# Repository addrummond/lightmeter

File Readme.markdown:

ARM gcc toolchain:

    https://launchpad.net/gcc-arm-embedded/+download

Programming known to work with OpenOCD 0.8.0.

See firmware/GDB_Readme.markdown.

Python 3 plus 'pypng' module required for build process.

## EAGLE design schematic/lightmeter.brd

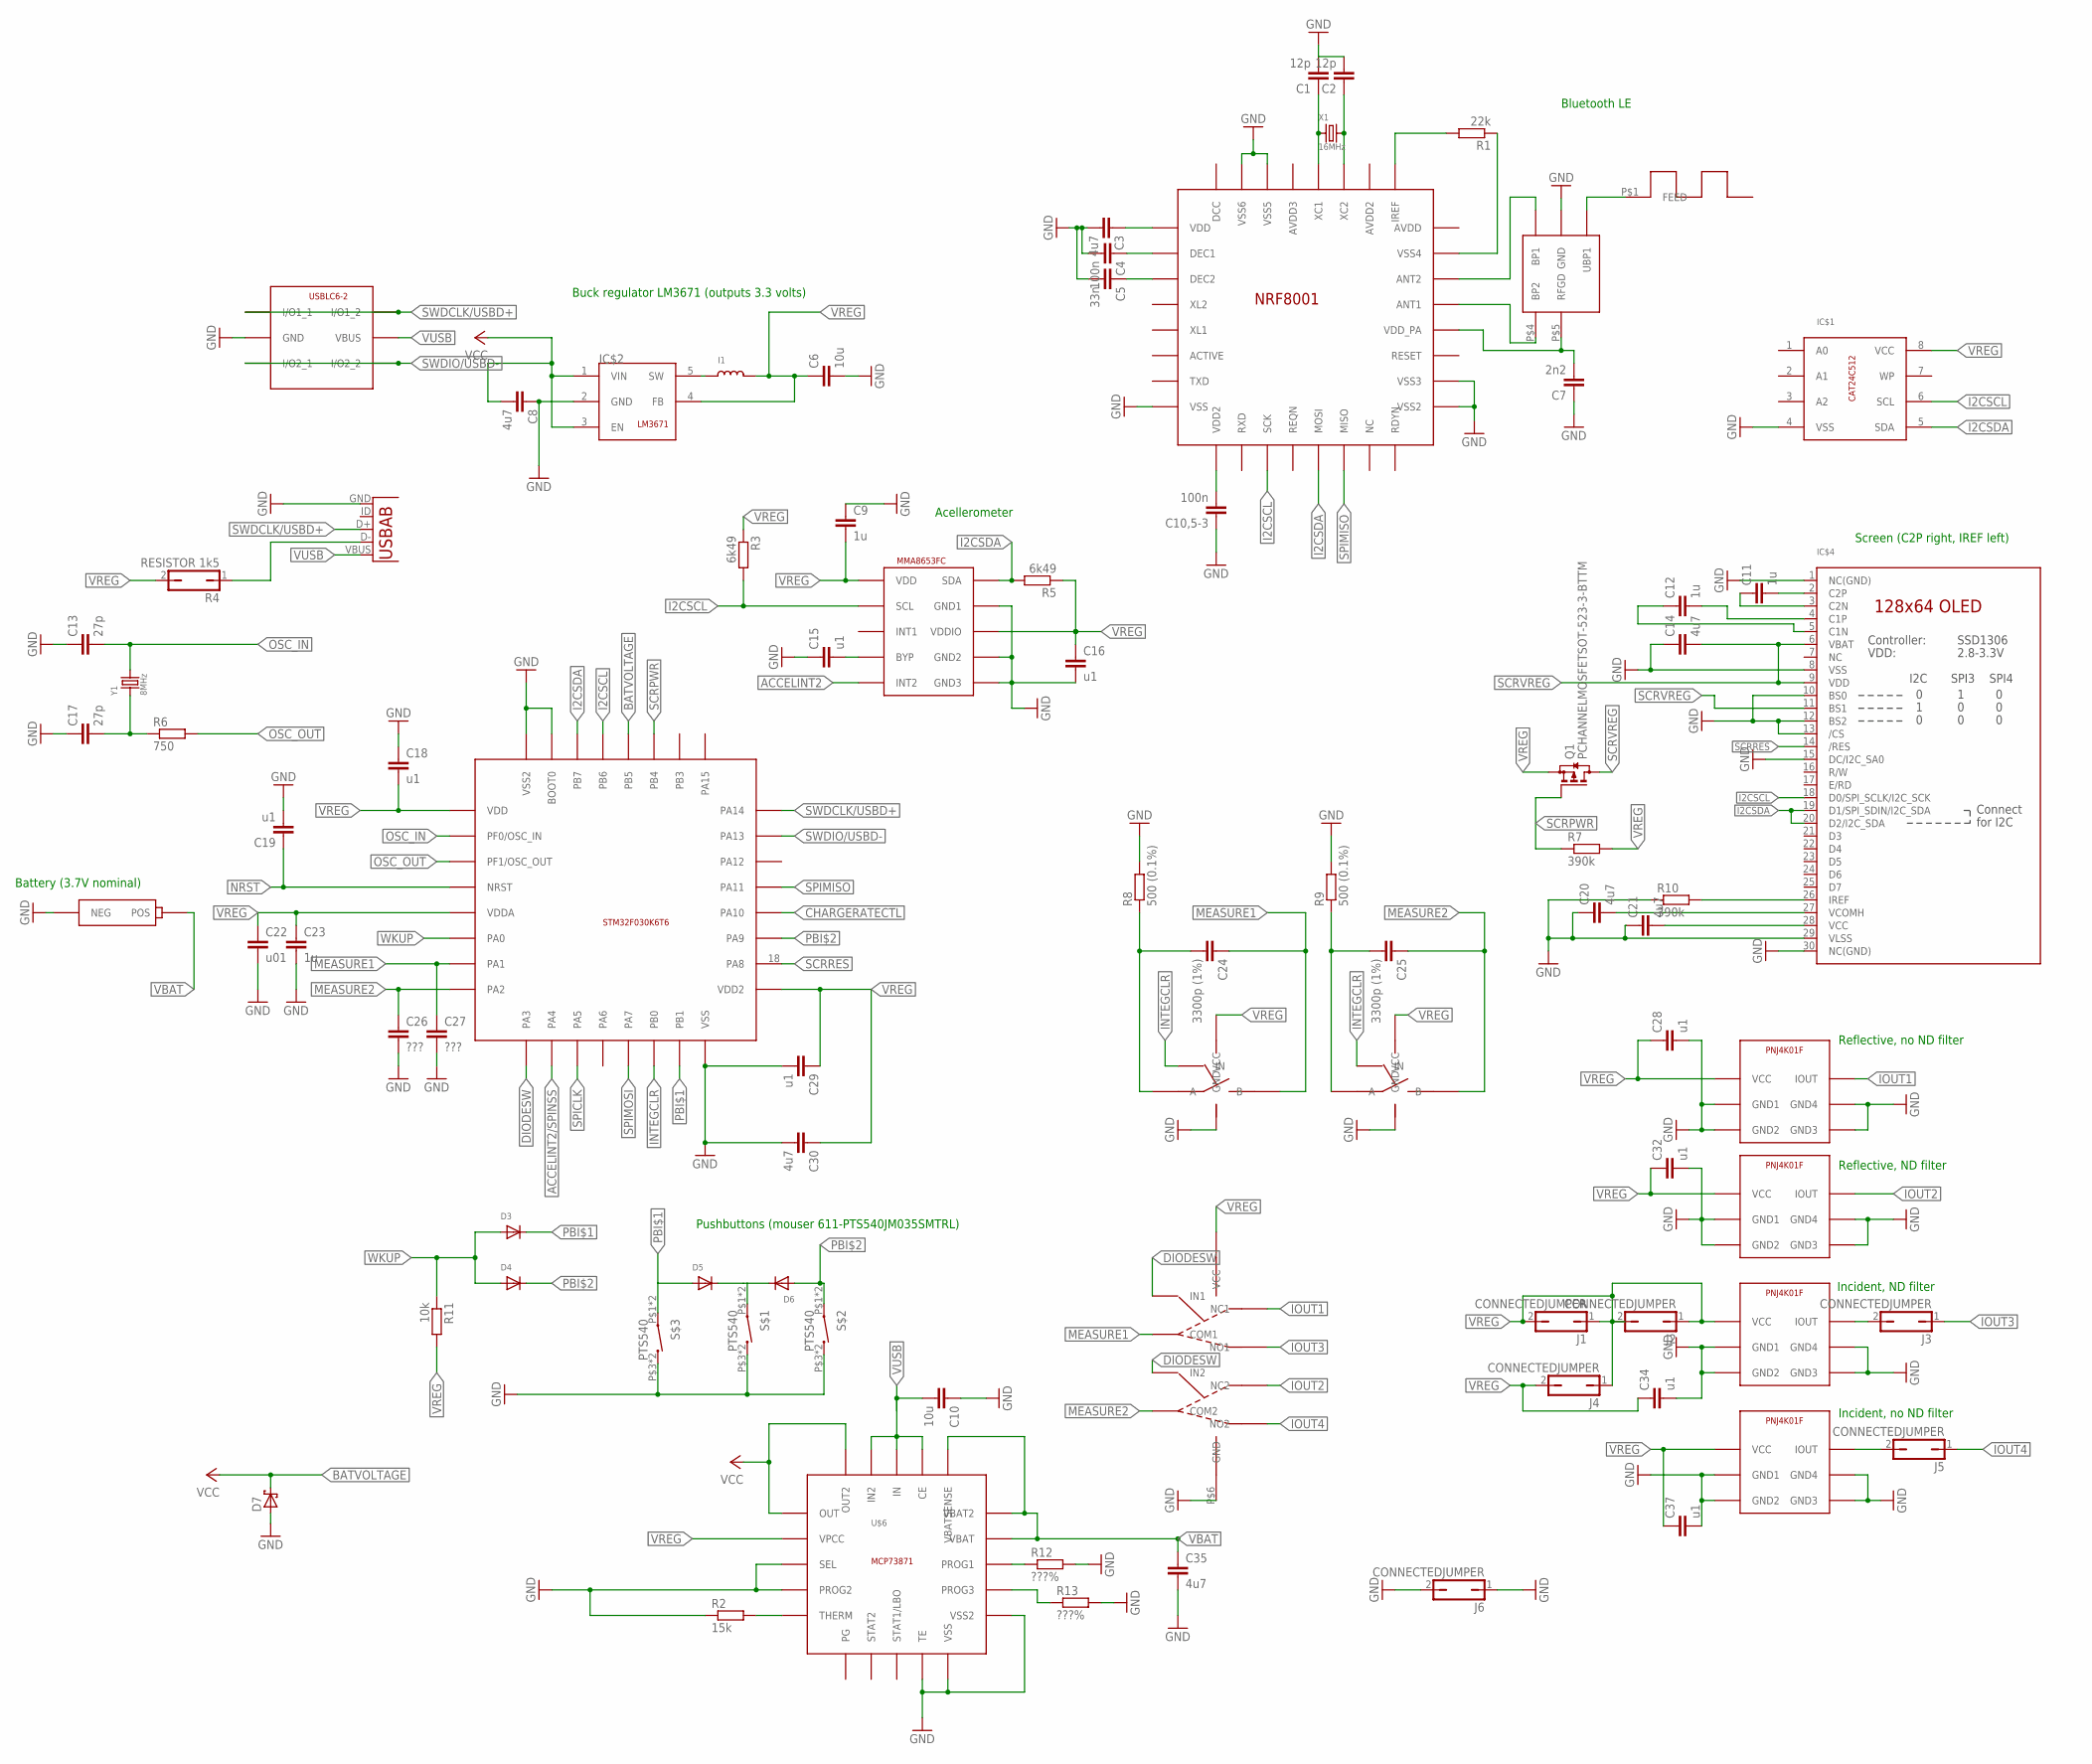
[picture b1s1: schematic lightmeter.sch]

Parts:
C1, C2: 12p; C0402
C3, C8, C14, C20, C21, C30, C35: 4u7; C0402
C4, C10,5-3: 100n; C0402
C5: 33n; C0402
C6: 10u; C0603
C7: 2n2; C0402
C9: 1u; C0603
C10: 10u; C0402
C11, C12: 1u; C0402
C13: 27p; GAP0402
C15, C16, C18, C19, C28, C29, C32, C34, C37: u1; C0402
C17: 27p; C0402
C22: u01; GAP0402
C23: 1u; GAP0603
C24, C25: 3300p (1%); C0603
C26, C27: ???; GAP0402
D3, D4, D5, D6: DIODESOD-323F; SOD-323F
D7: SCHOTTKY-DIODESOD-929; SOD-923
I1: CDRH2D14
IC$1: CAT24C512; TSSOP8
IC$2: LM3671; SOT23-5
IC$3: MMA8653; DFN-10
IC$4: DISP_OLED_UG-2864HSWEG010.96"; UG-2864HSWEG01_0.96IN_WRAPAROUND
IC$5: STM32F030K6T6; QFP-32
IC$6, IC$7: SN74LVC1G66; SOT-553-5
IC$8, IC$9, IC$11, IC$13: PNJ4K01F
IC$12: NLAS5223B; WQFN10
J1, J2, J3, J4, J5, J6: CONNECTEDJUMPER; JUMPER_R0402
Q1: PCHANNELMOSFETSOT-523-3-BTTM; SOT-523-3-BTTM
R1: 22k; R0402
R2: 15k; R0402
R3, R5: 6k49; R0402
R4: RESISTOR 1k5; JUMPER_R0402
R6: 750; R0402
R7, R10: 390k; R0402
R8, R9: 500 (0.1%); R0402
R11: 10k; R0402
R12, R13: ???%; R0402
S$1, S$2, S$3: PTS540; PTS540BTM
U1: USB-ABUSB-AB-MICRO-MIDMOUNT; USB-AB-MICRO-MIDMOUNT
U$1: 2450AT18A100
U$2: 2450BM14A00022450BM14A0002; 2450BM14A0002
U$3: NRF8001
U$4: USBLC6-2; SOT666
U$5: LIBAT; 78171-0002
U$6: MCP73871; QFN20
X1: 16MHz; CRYSTAL-2X1.6
Y1: 8MHz; CRYSTAL3.2X5MM

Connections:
ACCELINT2: IC$3.P$5 (INT2)
ACCELINT2/SPINSS: IC$5.10 (PA4)
ANT1CON: U$2.P$4 (BP2), U$3.P$21 (ANT1)
ANT2CON: U$2.P$3 (BP1), U$3.P$22 (ANT2)
ANTTRACE: U$1.P$1, U$2.P$1 (UBP1)
BATVOLTAGE: D7.P$2 (C), IC$5.28 (PB5)
CHARGERATECTL: IC$5.20 (PA10)
DIODESW: IC$5.9 (PA3), IC$12.P$4 (IN1), IC$12.P$8 (IN2)
GND: C1.2, C2.2, C3.2, C4.2, C5.2, C6.2, C7.1, C8.1, C9.1, C10.1, C10,5-3.1, C13.1, C14.1, C15.1, C16.2, C17.1, C18.1, C19.2, C20.1, C21.1, C22.2, C23.2, C26.2, C27.2, C28.2, C29.2, C30.2, C32.2, C34.2, C35.2, C37.2, D7.P$1 (A), IC$1.4 (VSS), IC$2.2 (GND), IC$3.P$6 (GND3), IC$3.P$7 (GND2), IC$3.P$9 (GND1), IC$4.1 (NC(GND)), IC$4.8 (VSS), IC$4.10 (BS0), IC$4.12 (BS2), IC$4.13 (/CS), IC$4.15 (DC/I2C_SA0), IC$4.29 (VLSS), IC$4.30 (NC(GND)), IC$5.16 (VSS), IC$5.31 (BOOT0), IC$5.32 (VSS2), IC$6.P$3 (GND), IC$7.P$3 (GND), IC$8.P$2 (GND1), IC$8.P$3 (GND2), IC$8.P$4 (GND3), IC$8.P$5 (GND4), IC$9.P$2 (GND1), IC$9.P$3 (GND2), IC$9.P$4 (GND3), IC$9.P$5 (GND4), IC$11.P$2 (GND1), IC$11.P$3 (GND2), IC$11.P$4 (GND3), IC$11.P$5 (GND4), IC$12.P$6 (GND), IC$13.P$2 (GND1), IC$13.P$3 (GND2), IC$13.P$4 (GND3), IC$13.P$5 (GND4), J6.1, J6.2, R2.1, R8.2, R9.2, R10.1, R12.2, R13.2, S$1.P$3 (2), S$1.P$4 (2), S$2.P$3 (2), S$2.P$4 (2), S$3.P$3 (2), S$3.P$4 (2), U1.GND, U$2.P$2 (GND), U$3.P$8 (VSS), U$3.P$17 (VSS2), U$3.P$18 (VSS3), U$3.P$30 (VSS5), U$3.P$31 (VSS6), U$3.P$33 (VSS), U$4.P$2 (GND), U$5.P$1 (NEG), U$6.P$3 (SEL), U$6.P$4 (PROG2), U$6.P$9 (TE), U$6.P$10 (VSS), U$6.P$11 (VSS2), U$6.P$21 (VSS2)
I2CSCL: IC$1.6 (SCL), IC$3.P$2 (SCL), IC$4.18 (D0/SPI_SCLK/I2C_SCK), IC$5.29 (PB6), R3.2, U$3.P$11 (SCK)
I2CSDA: IC$1.5 (SDA), IC$3.P$10 (SDA), IC$4.19 (D1/SPI_SDIN/I2C_SDA), IC$4.20 (D2/I2C_SDA), IC$5.30 (PB7), R5.2, U$3.P$13 (MOSI)
INTEGCLR: IC$5.14 (PB0), IC$6.P$4 (IN), IC$7.P$4 (IN)
IOUT1: IC$8.P$6 (IOUT), IC$12.P$5 (NC1)
IOUT2: IC$9.P$6 (IOUT), IC$12.P$7 (NC2)
IOUT3: IC$12.P$2 (NO1), J3.1
IOUT4: IC$12.P$10 (NO2), J5.1
MEASURE1: C24.1, C27.1, IC$5.7 (PA1), IC$6.P$2 (B), IC$12.P$3 (COM1)
MEASURE2: C25.1, C26.1, IC$5.8 (PA2), IC$7.P$2 (B), IC$12.P$9 (COM2)
unnamed: IC$11.P$6 (IOUT), J3.2
unnamed: IC$13.P$6 (IOUT), J5.2
unnamed: C24.2, IC$6.P$1 (A), R8.1
unnamed: R2.2, U$6.P$5 (THERM)
unnamed: C25.2, IC$7.P$1 (A), R9.1
unnamed: C15.2, IC$3.P$4 (BYP)
unnamed: C17.2, R6.1, Y1.P$1 (1)
unnamed: I1.P$1 (1), IC$2.5 (SW)
unnamed: C20.2, IC$4.27 (VCOMH)
unnamed: D5.C, D6.C, S$1.P$1 (1), S$1.P$2 (1)
unnamed: C11.2, IC$4.2 (C2P)
unnamed: C11.1, IC$4.3 (C2N)
unnamed: C7.2, U$2.P$5 (RFGD), U$3.P$20 (VDD_PA)
unnamed: R1.2, U$3.P$25 (IREF)
unnamed: IC$4.26 (IREF), R10.2
unnamed: R1.1, U$3.P$23 (VSS4)
unnamed: C5.1, U$3.P$3 (DEC2)
unnamed: C3.1, U$3.P$1 (VDD)
unnamed: C10,5-3.2, U$3.P$9 (VDD2)
unnamed: C12.1, IC$4.5 (C1N)
unnamed: C4.1, U$3.P$2 (DEC1)
unnamed: C1.1, U$3.P$28 (XC1), X1.P$1 (1)
unnamed: C12.2, IC$4.4 (C1P)
unnamed: C2.1, U$3.P$27 (XC2), X1.P$3 (2)
unnamed: C21.2, IC$4.28 (VCC)
unnamed: R12.1, U$6.P$13 (PROG1)
unnamed: R13.1, U$6.P$12 (PROG3)
NRST: C19.1, IC$5.4 (NRST)
OSC_IN: C13.2, IC$5.2 (PF0/OSC_IN), Y1.P$2 (2)
OSC_OUT: IC$5.3 (PF1/OSC_OUT), R6.2
PBI$1: D3.C, D5.A, IC$5.15 (PB1), S$3.P$1 (1), S$3.P$2 (1)
PBI$2: D4.C, D6.A, IC$5.19 (PA9), S$2.P$1 (1), S$2.P$2 (1)
SCRPWR: IC$5.27 (PB4), Q1.P$3 (G), R7.1
SCRRES: IC$4.14 (/RES), IC$5.18 (PA8)
SCRVREG: C14.2, IC$4.6 (VBAT), IC$4.9 (VDD), IC$4.11 (BS1), Q1.P$1 (D)
SPICLK: IC$5.11 (PA5)
SPIMISO: IC$5.21 (PA11), U$3.P$14 (MISO)
SPIMOSI: IC$5.13 (PA7)
SWDCLK/USBD+: IC$5.24 (PA14), U1.D+, U$4.P$1 (I/O1_1), U$4.P$6 (I/O1_2)
SWDIO/USBD-: IC$5.23 (PA13), U$4.P$3 (I/O2_1), U$4.P$4 (I/O2_2)
USBD-: R4.1, U1.D-
VBAT: C35.1, U$5.P$2 (POS), U$6.P$14 (VBAT), U$6.P$15 (VBAT2), U$6.P$16 (VBATSENSE)
VCC: C8.2, IC$2.1 (VIN), IC$2.3 (EN), U$6.P$1 (OUT), U$6.P$20 (OUT2)
VREG: C6.1, C9.2, C16.1, C18.2, C22.1, C23.1, C28.1, C29.1, C30.1, C32.1, C34.1, C37.1, I1.P$2 (2), IC$1.8 (VCC), IC$2.4 (FB), IC$3.P$1 (VDD), IC$3.P$8 (VDDIO), IC$5.1 (VDD), IC$5.5 (VDDA), IC$5.17 (VDD2), IC$6.P$5 (VCC), IC$7.P$5 (VCC), IC$8.P$1 (VCC), IC$9.P$1 (VCC), IC$11.P$1 (VCC), IC$12.P$1 (VCC), IC$13.P$1 (VCC), J1.1, J1.2, J2.1, J2.2, J4.1, J4.2, Q1.P$2 (S), R3.1, R4.2, R5.1, R7.2, R11.2, U$6.P$2 (VPCC)
VUSB: C10.2, U1.VBUS, U$4.P$5 (VBUS), U$6.P$17 (CE), U$6.P$18 (IN), U$6.P$19 (IN2)
WKUP: D3.A, D4.A, IC$5.6 (PA0), R11.1

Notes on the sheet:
Battery (3.7V nominal)
Buck regulator LM3671 (outputs 3.3 volts)
Pushbuttons (mouser 611-PTS540JM035SMTRL)
Screen (C2P right, IREF left)
Acellerometer
Reflective, no ND filter
Reflective, ND filter
Incident, ND filter
Incident, no ND filter
Bluetooth LE

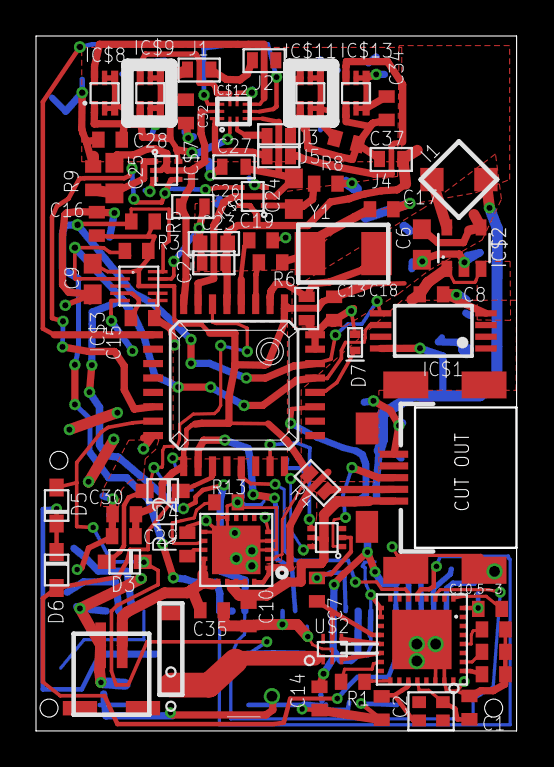
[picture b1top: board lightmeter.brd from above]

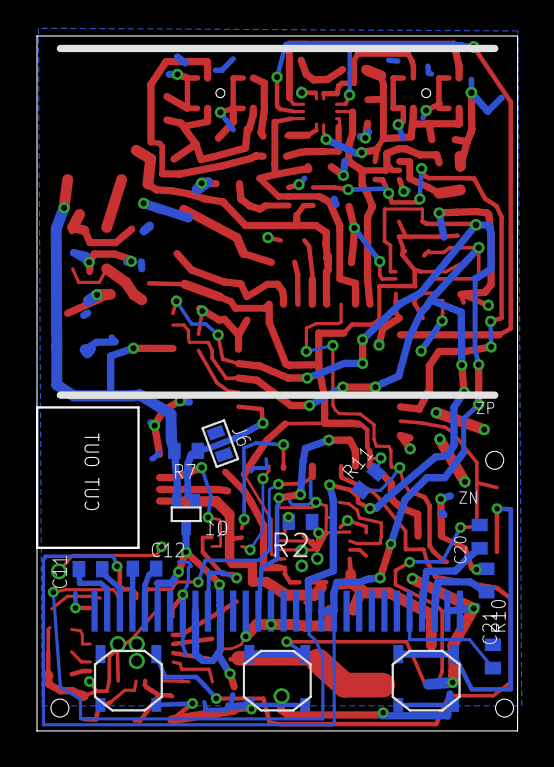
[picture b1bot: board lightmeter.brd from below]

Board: 2 copper layers, 26.7 x 38.6 mm, 85 parts (9 on the bottom side), 59 nets.

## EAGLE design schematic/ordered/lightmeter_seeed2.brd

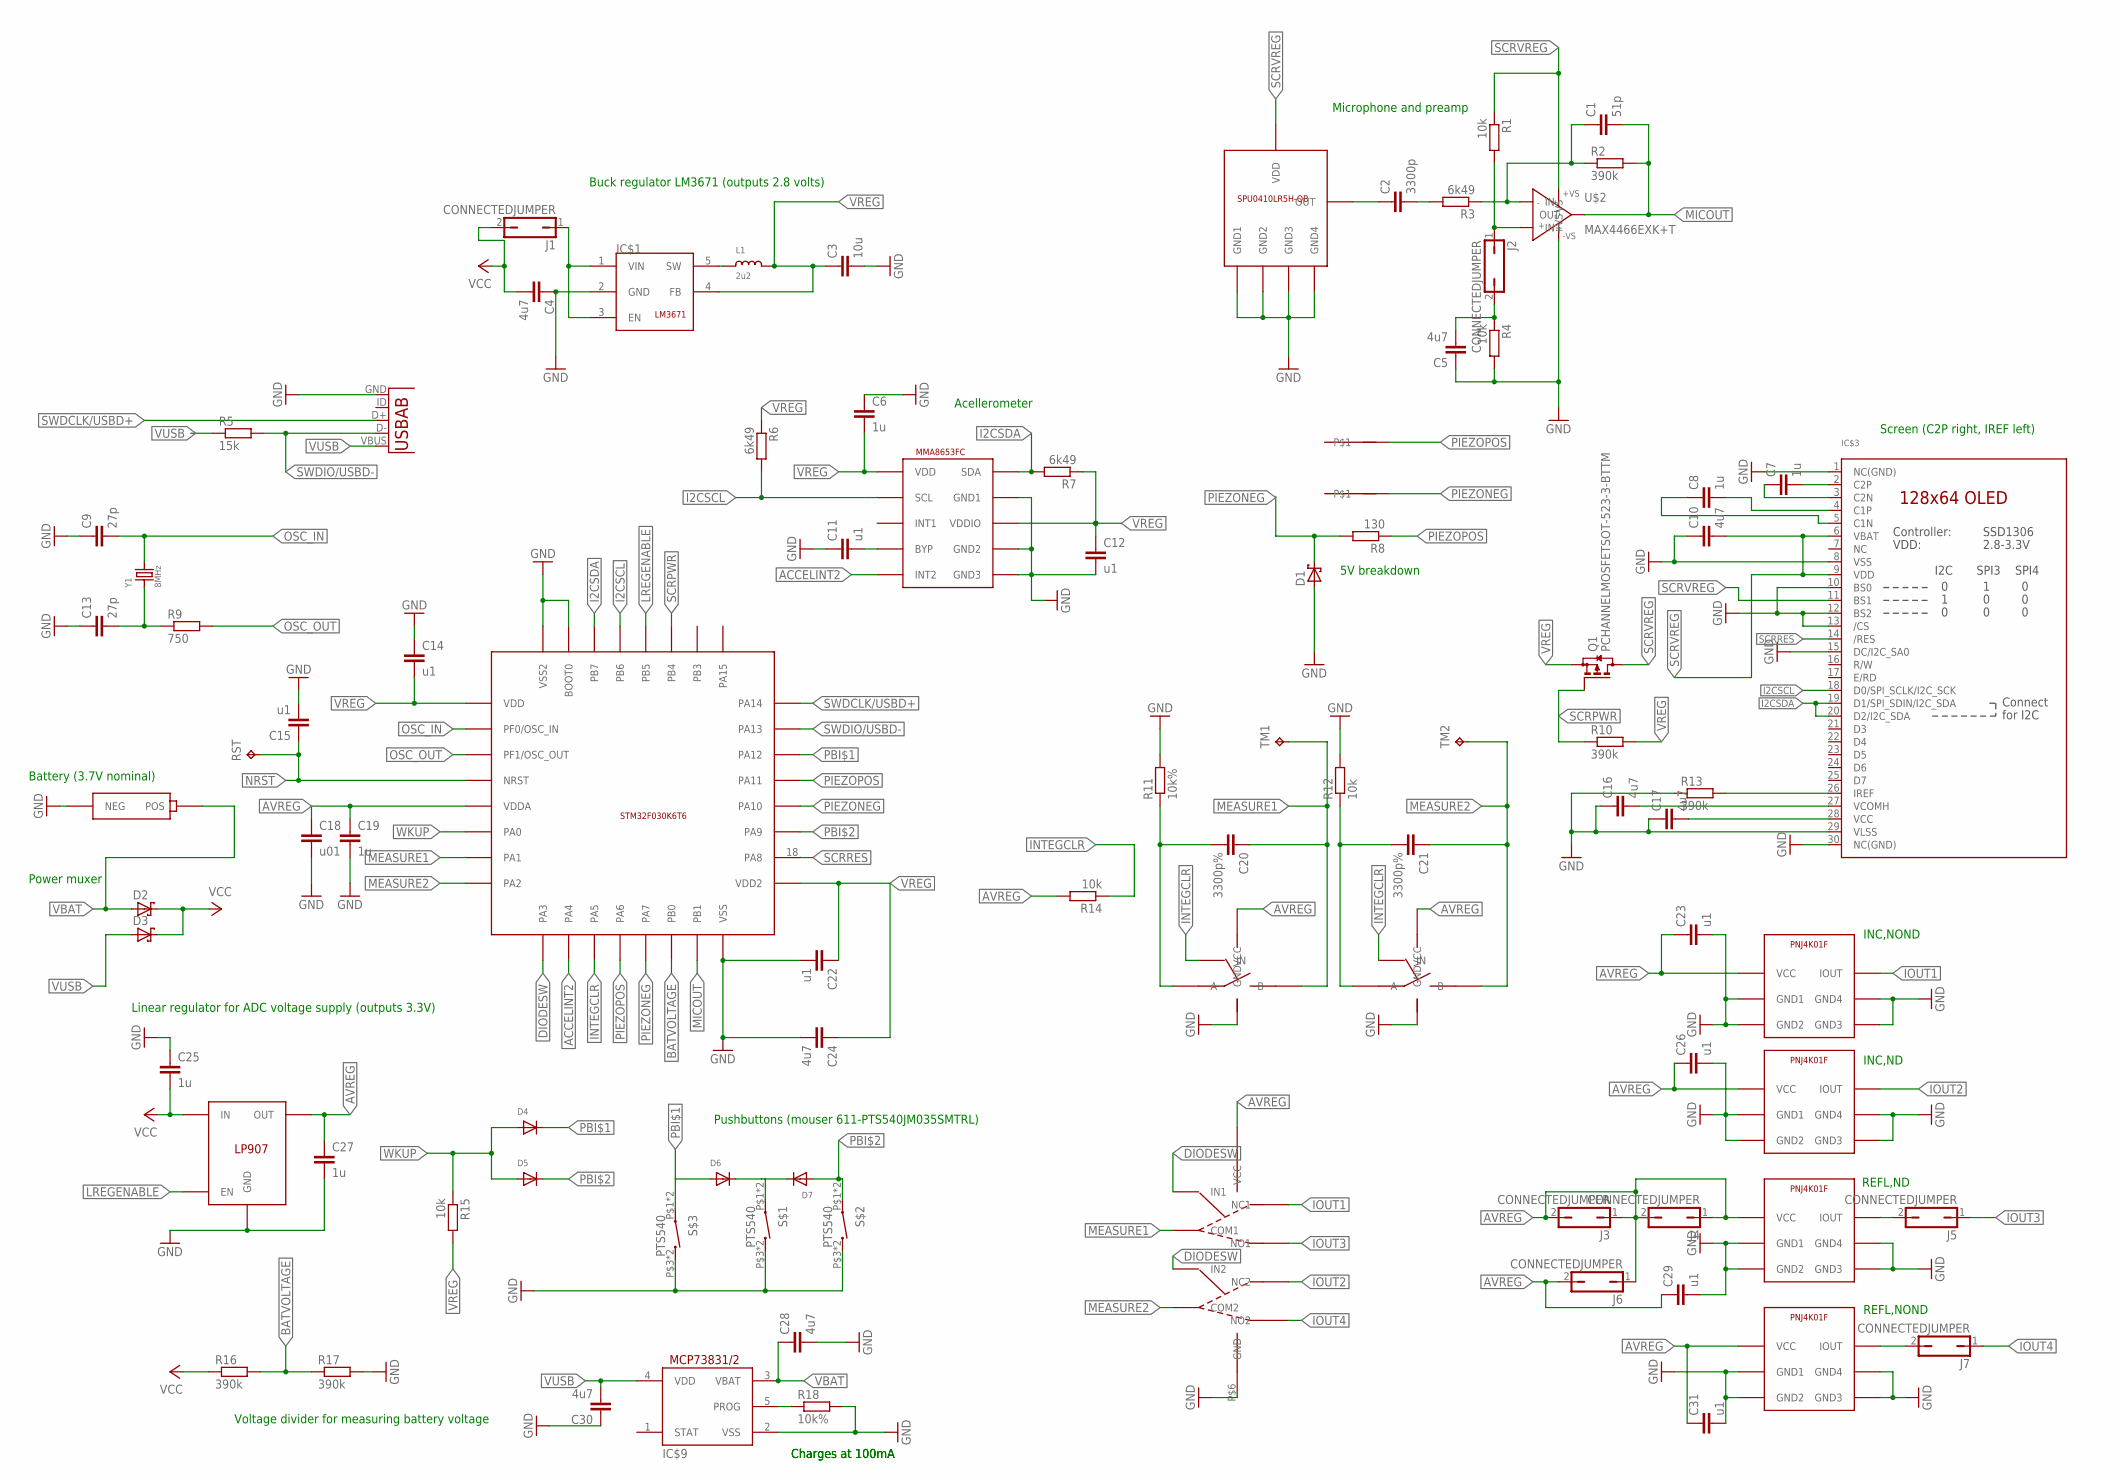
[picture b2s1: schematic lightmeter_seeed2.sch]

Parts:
C1: 51p; C0402
C2: 3300p; C0603
C3: 10u; C0402
C4, C5, C10, C16, C17, C24, C28, C30: 4u7; C0402
C6, C7, C8, C25, C27: 1u; C0603
C9: 27p; GAP0402
C11, C12, C14, C15, C22, C23, C26, C29, C31: u1; C0402
C13: 27p; C0402
C18: u01; GAP0402
C19: 1u; GAP0603
C20, C21: 3300p%; C0603
D1: SCHOTTKY-DIODESOD-923-BTTM; SOD-923-BTTM
D2, D3: SCHOTTKY-DIODESC-79; SC-79
D4, D5, D6, D7: DIODESOD-323F; SOD-323F
IC$1: LM3671; SOT23-5
IC$2: MMA8653; DFN-10
IC$3: DISP_OLED_UG-2864HSWEG010.96"; UG-2864HSWEG01_0.96IN_WRAPAROUND
IC$4: STM32F030K6T6; QFP-32
IC$5, IC$7, IC$8, IC$10: PNJ4K01F
IC$6: LP5907; SOT23-5L
IC$9: MCP73831/OT; SOT23-5L
J1, J2, J3, J4, J5, J6, J7: CONNECTEDJUMPER; JUMPER_R0402
L1: 2u2; _0603
Q1: PCHANNELMOSFETSOT-523-3-BTTM; SOT-523-3-BTTM
R1, R4, R12, R14, R15: 10k; R0402
R2, R10, R13, R17: 390k; R0402
R3, R6, R7: 6k49; R0402
R5: 15k; R0402
R8: 130; R0402
R9: 750; R0402
R11, R18: 10k%; R0402
R16: 390k; JUMPER_R0402
RST: TPB1,27; B1,27
S$1, S$2, S$3: PTS540; PTS540BTM
TM1, TM2: TPB1,27; B1,27
U1: USB-ABUSB-AB-MICRO-MIDMOUNT; USB-AB-MICRO-MIDMOUNT
U$1: SPU0410LR5H-QBSPU0410LRSH-QB; SPU0410LR5H-QB
U$2: MAX4466EXK+T; SC-70-5
U$3: LIBAT; 78171-0002
U$4, U$5: SN74LVC1G66; SOT-553-5
U$6: NLAS5223B; WQFN10
Y1: 8MHz; CRYSTAL3.2X5MM
ZN: WIREATTACHMENT; SMALLSQUAREWIREHOLE
ZP: WIREATTACHMENT; SMALLSQUAREWIREHOLE

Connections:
ACCELINT2: IC$2.P$5 (INT2), IC$4.10 (PA4)
AVREG: C18.1, C19.1, C23.1, C26.1, C27.1, C29.1, C31.1, IC$4.5 (VDDA), IC$5.P$1 (VCC), IC$6.5 (OUT), IC$7.P$1 (VCC), IC$8.P$1 (VCC), IC$10.P$1 (VCC), J3.1, J3.2, J4.1, J4.2, J6.1, J6.2, R14.2, U$4.P$5 (VCC), U$5.P$5 (VCC), U$6.P$1 (VCC)
BATVOLTAGE: IC$4.14 (PB0), R16.2, R17.1
DIODESW: IC$4.9 (PA3), U$6.P$4 (IN1), U$6.P$8 (IN2)
GND: C3.2, C4.1, C5.1, C6.1, C9.1, C10.1, C11.1, C12.2, C13.1, C14.1, C15.2, C16.1, C17.1, C18.2, C19.2, C22.2, C23.2, C24.2, C25.1, C26.2, C27.2, C28.2, C29.2, C30.1, C31.2, D1.P$1 (A), IC$1.2 (GND), IC$2.P$6 (GND3), IC$2.P$7 (GND2), IC$2.P$9 (GND1), IC$3.1 (NC(GND)), IC$3.8 (VSS), IC$3.10 (BS0), IC$3.12 (BS2), IC$3.13 (/CS), IC$3.15 (DC/I2C_SA0), IC$3.29 (VLSS), IC$3.30 (NC(GND)), IC$4.16 (VSS), IC$4.31 (BOOT0), IC$4.32 (VSS2), IC$5.P$2 (GND1), IC$5.P$3 (GND2), IC$5.P$4 (GND3), IC$5.P$5 (GND4), IC$6.2 (GND), IC$7.P$2 (GND1), IC$7.P$3 (GND2), IC$7.P$4 (GND3), IC$7.P$5 (GND4), IC$8.P$2 (GND1), IC$8.P$3 (GND2), IC$8.P$4 (GND3), IC$8.P$5 (GND4), IC$9.2 (VSS), IC$10.P$2 (GND1), IC$10.P$3 (GND2), IC$10.P$4 (GND3), IC$10.P$5 (GND4), R4.2, R11.2, R12.2, R13.1, R17.2, R18.2, S$1.P$3 (2), S$1.P$4 (2), S$2.P$3 (2), S$2.P$4 (2), S$3.P$3 (2), S$3.P$4 (2), U1.GND, U$1.P$2 (GND1), U$1.P$3 (GND2), U$1.P$5 (GND3), U$1.P$6 (GND4), U$2.P$2 (-VS), U$3.P$1 (NEG), U$4.P$3 (GND), U$5.P$3 (GND), U$6.P$6 (GND)
I2CSCL: IC$2.P$2 (SCL), IC$3.18 (D0/SPI_SCLK/I2C_SCK), IC$4.29 (PB6), R6.2
I2CSDA: IC$2.P$10 (SDA), IC$3.19 (D1/SPI_SDIN/I2C_SDA), IC$3.20 (D2/I2C_SDA), IC$4.30 (PB7), R7.2
INTEGCLR: IC$4.11 (PA5), R14.1, U$4.P$4 (IN), U$5.P$4 (IN)
IOUT1: IC$5.P$6 (IOUT), U$6.P$5 (NC1)
IOUT2: IC$7.P$6 (IOUT), U$6.P$7 (NC2)
IOUT3: J5.1, U$6.P$2 (NO1)
IOUT4: J7.1, U$6.P$10 (NO2)
LREGENABLE: IC$4.28 (PB5), IC$6.3 (EN)
MEASURE1: C20.1, IC$4.7 (PA1), TM1.TP, U$4.P$2 (B), U$6.P$3 (COM1)
MEASURE2: C21.1, IC$4.8 (PA2), TM2.TP, U$5.P$2 (B), U$6.P$9 (COM2)
MICOUT: C1.2, IC$4.15 (PB1), R2.2, U$2.P$4 (OUT)
unnamed: IC$8.P$6 (IOUT), J5.2
unnamed: IC$10.P$6 (IOUT), J7.2
unnamed: C20.2, R11.1, U$4.P$1 (A)
unnamed: IC$1.1 (VIN), IC$1.3 (EN), J1.1
unnamed: IC$9.5 (PROG), R18.1
unnamed: C21.2, R12.1, U$5.P$1 (A)
unnamed: C11.2, IC$2.P$4 (BYP)
unnamed: C13.2, R9.1, Y1.P$1 (1)
unnamed: IC$1.5 (SW), L1.1
unnamed: C16.2, IC$3.27 (VCOMH)
unnamed: D6.C, D7.C, S$1.P$1 (1), S$1.P$2 (1)
unnamed: C2.1, U$1.P$1 (OUT)
unnamed: C7.2, IC$3.2 (C2P)
unnamed: C7.1, IC$3.3 (C2N)
unnamed: C2.2, R3.2
unnamed: C1.1, R2.1, R3.1, U$2.P$3 (IN-)
unnamed: IC$3.26 (IREF), R13.2
unnamed: J2.1, R1.2, U$2.P$1 (IN+)
unnamed: C5.2, J2.2, R4.1
unnamed: C8.1, IC$3.5 (C1N)
unnamed: C8.2, IC$3.4 (C1P)
unnamed: C17.2, IC$3.28 (VCC)
NRST: C15.1, IC$4.4 (NRST), RST.TP
OSC_IN: C9.2, IC$4.2 (PF0/OSC_IN), Y1.P$2 (2)
OSC_OUT: IC$4.3 (PF1/OSC_OUT), R9.2
PBI$1: D4.C, D6.A, IC$4.22 (PA12), S$3.P$1 (1), S$3.P$2 (1)
PBI$2: D5.C, D7.A, IC$4.19 (PA9), S$2.P$1 (1), S$2.P$2 (1)
PIEZONEG: D1.P$2 (C), IC$4.13 (PA7), IC$4.20 (PA10), R8.2, ZN.P$1
PIEZOPOS: IC$4.12 (PA6), IC$4.21 (PA11), R8.1, ZP.P$1
SCRPWR: IC$4.27 (PB4), Q1.P$2 (G), R10.1
SCRRES: IC$3.14 (/RES), IC$4.18 (PA8)
SCRVREG: C10.2, IC$3.6 (VBAT), IC$3.9 (VDD), IC$3.11 (BS1), Q1.P$1 (D), R1.1, U$1.P$4 (VDD), U$2.P$5 (+VS)
SWDCLK/USBD+: IC$4.24 (PA14), U1.D+
SWDIO/USBD-: IC$4.23 (PA13), R5.2, U1.D-
VBAT: C28.1, D2.P$2 (A), IC$9.3 (VBAT), U$3.P$2 (POS)
VCC: C4.2, C25.2, D2.P$1 (C), D3.P$1 (C), IC$6.1 (IN), J1.2, R16.1
VREG: C3.1, C6.2, C12.1, C14.2, C22.1, C24.1, IC$1.4 (FB), IC$2.P$1 (VDD), IC$2.P$8 (VDDIO), IC$4.1 (VDD), IC$4.17 (VDD2), L1.2, Q1.P$3 (S), R6.1, R7.1, R10.2, R15.2
VUSB: C30.2, D3.P$2 (A), IC$9.4 (VDD), R5.1, U1.VBUS
WKUP: D4.A, D5.A, IC$4.6 (PA0), R15.1

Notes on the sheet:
Battery (3.7V nominal)
Buck regulator LM3671 (outputs 2.8 volts)
Pushbuttons (mouser 611-PTS540JM035SMTRL)
Screen (C2P right, IREF left)
Power muxer
Charges at 100mA
Acellerometer
Linear regulator for ADC voltage supply (outputs 3.3V)
Voltage divider for measuring battery voltage
INC,NOND
INC,ND
REFL,ND
REFL,NOND
5V breakdown
Microphone and preamp

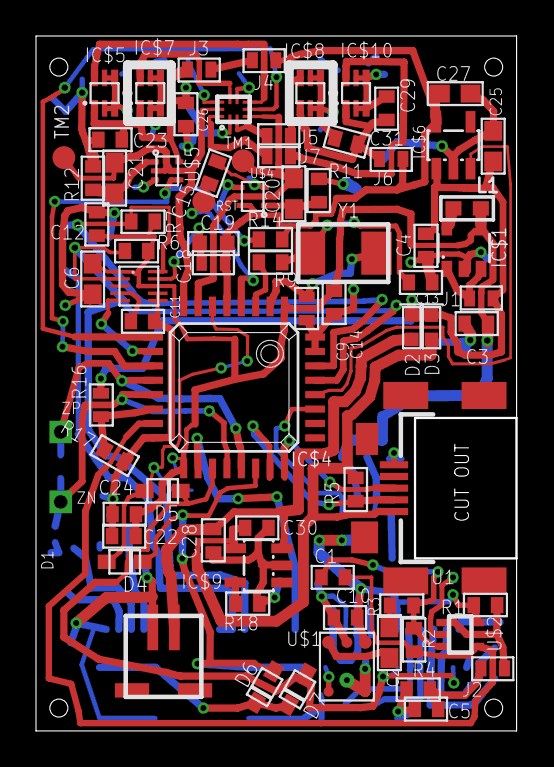
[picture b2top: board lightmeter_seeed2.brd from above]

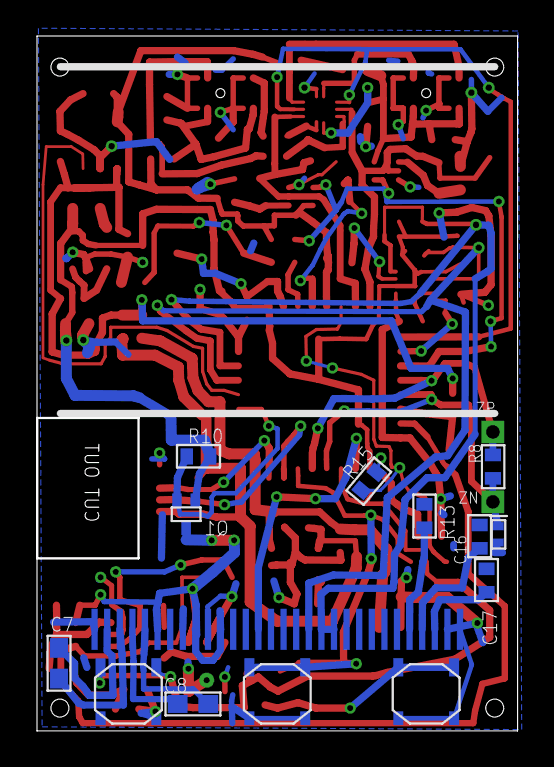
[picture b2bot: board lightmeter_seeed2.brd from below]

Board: 2 copper layers, 26.7 x 38.6 mm, 91 parts (8 on the bottom side), 55 nets.

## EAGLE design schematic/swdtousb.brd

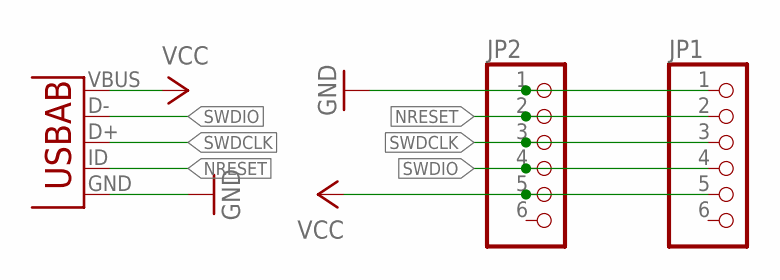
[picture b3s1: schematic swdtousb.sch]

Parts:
JP1, JP2: PINHD-1X6; 1X06
U1: USB-AB; USB-AB-MICRO

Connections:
GND: JP1.1, JP2.1, U1.GND
NRESET: JP1.2, JP2.2, U1.ID (USBID)
SWDCLK: JP1.3, JP2.3, U1.D+
SWDIO: JP1.4, JP2.4, U1.D-
VCC: JP1.5, JP2.5, U1.VBUS

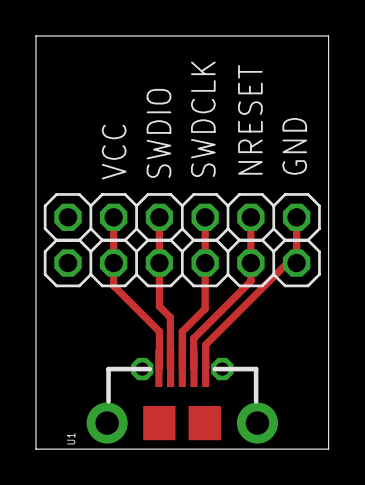
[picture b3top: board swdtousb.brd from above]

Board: 2 copper layers, 16.3 x 23.0 mm, 3 parts (0 on the bottom side), 5 nets.

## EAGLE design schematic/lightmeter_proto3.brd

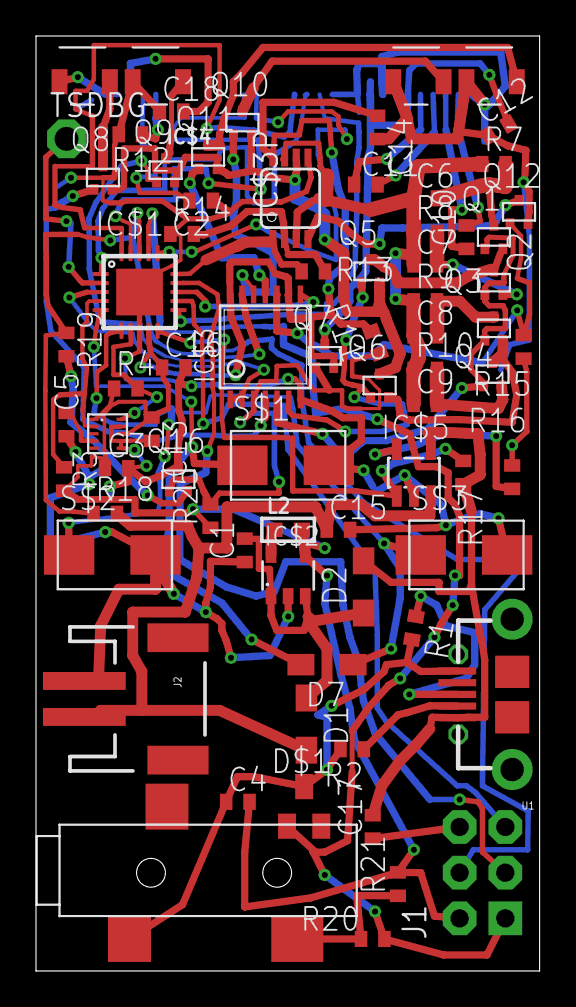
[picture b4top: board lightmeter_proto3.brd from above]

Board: 2 copper layers, 28.0 x 51.9 mm, 75 parts (0 on the bottom side), 60 nets.

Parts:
C1, C15, C17: 4u7; C0402
C2, C18: 2µ2; C0402
C3: 1u; C0402
C4, C5, C13: u1; C0402
C6, C7, C8, C9, C12: 4µ7; C0402
C10, C11: 1µ; C0402
C14, C16: µ1; C0402
D1, D2, D7: SOD323-W
D8, D9, D10, D11: VEMD2523SLX01
D$1: GSOT04-E3-08; SOT23
IC$1: ATTINY1634MLF20; MLF20
IC$2: LM3671; SOT23-5
IC$3: SN74HC164TSSOP-14; TSSOP14
IC$3P: AD8542RM; MSOP08
IC$4: UG-2864HSWEG01_0.96IN_WRAPAROUND
IC$5: MCP73831/OT; SOT23-5L
IC$6: MMA8653; DFN-10
J1: AVR_SPI_PRG_6NS; 2X3-NS
J2: JST-2-SMD
L2: 2µ2; _0603
Q1, Q3, Q5, Q8, Q9, Q10, Q11, Q12: NCHANNELMOSFET; SOT-416-3
Q2, Q4, Q6, Q7, Q16: PCHANNELMOSFET; SOT-416-3
R1, R2: 15K; R0402
R3, R4: 1K; R0402
R7: 750k%; R0402
R8: 97.5k%; R0402
R9: 13k%; R0402
R10: 1k6%; R0402
R11, R15: 10k; R0402
R12: 390k; R0402
R13, R14: ???%; R0402
R16, R18: 10K%; R0402
R17, R25: 10K; R0402
R19: 6K8%; R0402
R20: 6k8; R0402
R21: 16K; R0402
S$1, S$2, S$3: SMALLPUSHBUTTON; BUTTON
TSDBG: TPPAD1-13; P1-13
U1: USB-AB-MICRO
U$3: 3TRS_PHONE_JACK; 3TRS-SMD

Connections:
ACCSCL: IC$1.4, IC$6.P$2, R3.2
ACCSDA: IC$1.7, IC$6.P$10, R4.2
AVRMISO/FLASHSYNC: D$1.1, IC$1.17, J1.1, R20.1
AVRMOSI/BATVOLTAGE: IC$1.18, J1.4, R18.1, R19.2
AVRRST: IC$1.12, J1.5
AVRSCK: IC$1.14, J1.3
BATSTAT: IC$1.10, IC$5.1, R17.1
DIODESW$1: IC$3.4, Q8.P$1
DIODESW$2: IC$3.13, Q9.P$1
DIODESW$3: IC$3.12, Q10.P$1
DIODESW$4: IC$3.11, Q11.P$1
GND: C1.1, C2.1, C3.2, C4.1, C5.1, C12.1, C13.2, C14.2, C15.2, C16.2, C17.1, C18.1, D8.P$1, D9.P$1, D10.P$1, D11.P$1, D$1.3, IC$1.8, IC$1.GND, IC$2.2, IC$3.7, IC$3P.5, IC$4.1, IC$4.8, IC$4.10, IC$4.11, IC$4.12, IC$4.29, IC$4.30, IC$5.2, IC$6.P$6, IC$6.P$7, IC$6.P$9, J1.6, J2.1, Q12.P$2, Q16.P$3, R1.1, R2.1, R12.1, R14.1, R15.2, R16.2, S$1.P$3, S$2.P$3, S$3.P$3, U1.GND, U$3.P$1
unnamed: D8.P$2, Q8.P$3
unnamed: D9.P$2, Q9.P$3
unnamed: C7.2, Q2.P$2, R8.2
unnamed: C9.2, Q4.P$2, R10.2
unnamed: IC$5.5, R16.1
unnamed: IC$3P.4, Q12.P$3
unnamed: C5.2, IC$6.P$4
unnamed: D10.P$2, Q10.P$3
unnamed: IC$2.5, L2.1
unnamed: D11.P$2, Q11.P$3
unnamed: C2.2, IC$4.27
unnamed: C8.2, Q3.P$3, R9.2
unnamed: C10.2, IC$4.2
unnamed: C10.1, IC$4.3
unnamed: Q16.P$2, R19.1
unnamed: IC$4.26, R12.2
unnamed: Q1.P$2, Q2.P$3, Q5.P$3
unnamed: C6.2, Q1.P$3, R7.2
unnamed: Q3.P$2, Q4.P$3, Q6.P$2
unnamed: IC$1.2, TSDBG.TP
unnamed: C11.1, IC$4.5
unnamed: IC$3P.6, Q5.P$2, Q6.P$3, Q8.P$2, Q9.P$2, Q10.P$2, Q11.P$2
unnamed: C11.2, IC$4.4
unnamed: R1.2, U1.D+
unnamed: R20.2, R21.1, U$3.P$3
unnamed: C18.2, IC$4.28
unnamed: IC$3P.2, R13.2, R14.2
unnamed: R2.2, U1.D-
OAOUT1: C6.1, C7.1, C8.1, C9.1, IC$3P.3, IC$3P.7, R7.1, R8.1, R9.1, R10.1
OAOUT2: IC$1.15, IC$3P.1, R13.1
OAPWR: IC$3.10, Q12.P$1, R15.1
PBI$1: D7.A, IC$1.5, S$1.P$1
PBI$2: D7.C, IC$1.6, S$2.P$1, S$3.P$1
SCRCLK: IC$1.16, IC$4.18
SCRCS: IC$1.11, IC$4.13
SCRDAT: IC$1.19, IC$4.19
SCRDC: IC$1.20, IC$4.15
SCRPWR: IC$3.3, Q7.P$1, Q16.P$1, R11.1, R25.2
SCRRES: IC$1.1, IC$4.14
SCRVREG: C12.2, IC$4.6, IC$4.9, Q7.P$3
SRA: IC$1.3, IC$3.1, IC$3.2
SRCLK: IC$1.13, IC$3.8
STG$1: IC$3.5, Q1.P$1, Q2.P$1, Q3.P$1, Q4.P$1
STG$2: IC$3.6, Q5.P$1, Q6.P$1
VBAT: C15.1, D1.A, IC$5.3, J2.2, R18.2
VCC: C1.2, D1.C, D2.C, IC$2.1, IC$2.3
VREG: C3.1, C4.2, C13.1, C14.1, C16.1, IC$1.9, IC$2.4, IC$3.9, IC$3.14, IC$3P.8, IC$6.P$1, IC$6.P$8, J1.2, L2.2, Q7.P$2, R3.1, R4.1, R11.2, R21.2, R25.1
VUSB: C17.2, D2.A, IC$5.4, R17.2, U1.VBUS

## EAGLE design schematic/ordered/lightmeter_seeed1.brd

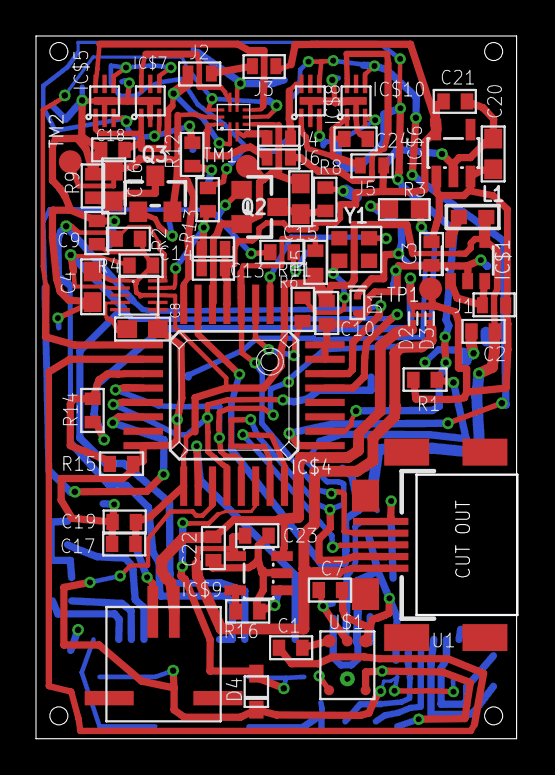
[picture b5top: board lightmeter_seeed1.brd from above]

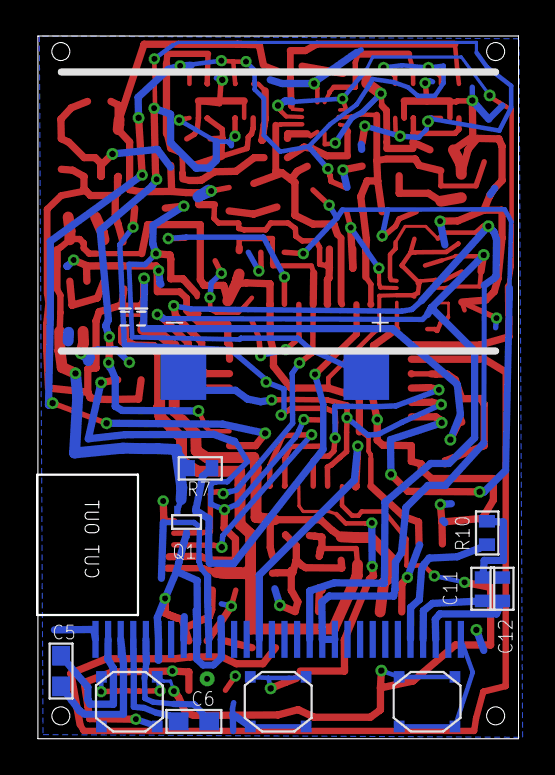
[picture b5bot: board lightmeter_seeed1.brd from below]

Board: 2 copper layers, 26.7 x 39.0 mm, 76 parts (7 on the bottom side), 50 nets.

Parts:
C1, C9, C10, C17, C18, C24: u1; C0402
C2: 10u; C0402
C3, C7, C19, C22, C23: 4u7; C0402
C4, C5, C6, C20: 1u; C0603
C8: u1; C0603
C11, C12: 2u2; C0402
C13: u01; GAP0402
C14: 1u; GAP0402
C15, C16: 3300p%; C0603
C21: 1u; C0402
D1: SOD-923
D2, D3: X3-DFN0603-2
D4: SOD-323F
IC$1: LM3671; SOT23-5
IC$2: MMA8653; DFN-10
IC$3: UG-2864HSWEG01_0.96IN_WRAPAROUND
IC$4: QFP-32
IC$5, IC$7, IC$8, IC$10: NOA1212; CUDFN6
IC$6: LP5907; SOT23-5L
IC$9: MCP73831/OT; SOT23-5L
J1, J2, J3, J4, J5, J6: CONNECTEDJUMPER; JUMPER_R0402
L1: 2u2; _0603
Q1: PCHANNELMOSFETSOT-523-3; SOT-523-3
Q2, Q3: SOT23-WIDE
R1: 15k; R0402
R2, R4: 1k; R0402
R3: 130; R0603
R5, R7, R8, R9, R11, R12, R13: 10k; R0402
R6: ??; R0402
R10: 390k; R0402
R14, R15: 500k; R0402
R16: 10k%; R0402
S$1, S$2, S$3: PTS540; PTS540BTM
TM1, TM2: TPB1,27; B1,27
TP1: TPB1,27; B1,27
U1: USB-AB-MICRO-MIDMOUNT
U$1: SPU0410LR5H-QBSPU0410LRSH-QB; SPU0410LR5H-QB
U$2: PIEZOBENDER165
U$3: LIBAT; 78171-0002
U$4: NLAS5223B; WQFN10
Y1: CRYSTAL_2.5X2

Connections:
AUDIOIN: D1.P$2, R3.2, U$2.P$2
AVREG: C13.1, C14.1, C18.1, C21.1, C24.1, IC$4.5, IC$5.P$1, IC$6.5, IC$7.P$1, IC$8.P$1, IC$10.P$1, J2.1, J2.2, J3.1, J3.2, J5.1, J5.2, U$4.P$1
BATVOLTAGE: IC$4.11, R14.2, R15.1
DIODESW: IC$4.9, U$4.P$4, U$4.P$8
GB1: IC$4.26, IC$5.P$3, IC$7.P$3, IC$8.P$3, IC$10.P$3, R12.2
GB2: IC$4.25, IC$5.P$4, IC$7.P$4, IC$8.P$4, IC$10.P$4, R13.2
GND: C2.2, C3.1, C4.1, C7.1, C8.1, C9.2, C10.1, C11.1, C12.1, C13.2, C14.2, C17.2, C18.2, C19.2, C20.1, C21.2, C22.2, C23.1, C24.2, D1.P$1, IC$1.2, IC$2.P$6, IC$2.P$7, IC$2.P$9, IC$3.1, IC$3.8, IC$3.10, IC$3.12, IC$3.15, IC$3.29, IC$3.30, IC$4.16, IC$4.31, IC$4.32, IC$5.P$2, IC$5.P$7, IC$6.2, IC$7.P$2, IC$7.P$7, IC$8.P$2, IC$8.P$7, IC$9.2, IC$10.P$2, IC$10.P$7, R8.2, R9.2, R10.1, R11.2, R12.1, R13.1, R15.2, R16.2, S$1.P$3, S$1.P$4, S$2.P$3, S$2.P$4, S$3.P$3, S$3.P$4, U1.GND, U$1.P$2, U$1.P$3, U$1.P$5, U$1.P$6, U$3.P$1, U$4.P$6
I2CSCL: IC$2.P$2, IC$3.18, IC$4.29, R4.2
I2CSDA: IC$2.P$10, IC$3.19, IC$3.20, IC$4.30, R2.2
INTEGCLR: IC$4.14, Q2.1, Q3.1, R11.1
IOUT1: IC$5.P$6, U$4.P$5
IOUT2: IC$7.P$6, U$4.P$7
IOUT3: J4.1, U$4.P$2
IOUT4: J6.1, U$4.P$10
MEASURE1: C15.1, IC$4.6, Q2.2, TM1.TP, U$4.P$3
MEASURE2: C16.1, IC$4.8, Q3.2, TM2.TP, U$4.P$9
MICOUT: C1.2, IC$4.10
unnamed: IC$8.P$6, J4.2
unnamed: IC$10.P$6, J6.2
unnamed: C15.2, Q2.3, R8.1
unnamed: IC$1.1, IC$1.3, J1.1
unnamed: IC$9.5, R16.1
unnamed: C16.2, Q3.3, R9.1
unnamed: C8.2, IC$2.P$4
unnamed: IC$4.2, Y1.3
unnamed: IC$4.3, R6.2
unnamed: IC$1.5, L1.1
unnamed: R6.1, Y1.1
unnamed: C11.2, IC$3.27
unnamed: C1.1, U$1.P$1
unnamed: C5.2, IC$3.2
unnamed: C5.1, IC$3.3
unnamed: IC$3.26, R10.2
unnamed: C6.1, IC$3.5
unnamed: C6.2, IC$3.4
unnamed: C12.2, IC$3.28
NRST: IC$4.4, R5.1, U1.ID
PBI$1: D4.A, IC$4.22, S$3.P$1, S$3.P$2
PBI$2: D4.C, IC$4.19, S$1.P$1, S$1.P$2, S$2.P$1, S$2.P$2
PIEZONEG: IC$4.13, IC$4.20, U$2.P$1
PIEZOPOS: IC$4.12, IC$4.21, R3.1
SCRPWR: IC$4.7, Q1.P$2, R7.1
SCRRES: IC$3.14, IC$4.18
SCRVREG: C7.2, IC$3.6, IC$3.9, IC$3.11, Q1.P$1, U$1.P$4
SWDCLK/USBD+: IC$4.24, U1.D+
SWDIO/USBD-: IC$4.23, R1.2, U1.D-
VBAT: C22.1, D2.P$1, IC$9.3, U$3.P$2
VCC: C3.2, C20.2, D2.P$2, D3.P$2, IC$6.1, IC$6.3, J1.2, R1.1, R14.1, TP1.TP
VREG: C2.1, C4.2, C9.1, C10.2, C17.1, C19.1, IC$1.4, IC$2.P$1, IC$2.P$8, IC$4.1, IC$4.17, L1.2, Q1.P$3, R2.1, R4.1, R5.2, R7.2
VUSB: C23.2, D3.P$1, IC$9.4, U1.VBUS

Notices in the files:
parts and their libraries:
microbuilder: This work is placed in the public domain, and may be freely used for commercial and non-commercial work with the following conditions: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
SparkFun-Connectors: Licensing: Creative Commons ShareAlike 4.0 International - https://creativecommons.org/licenses/by-sa/4.0
